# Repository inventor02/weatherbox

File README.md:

# Weatherbox

A work-in-progress hardware project to display the weather at your current location.

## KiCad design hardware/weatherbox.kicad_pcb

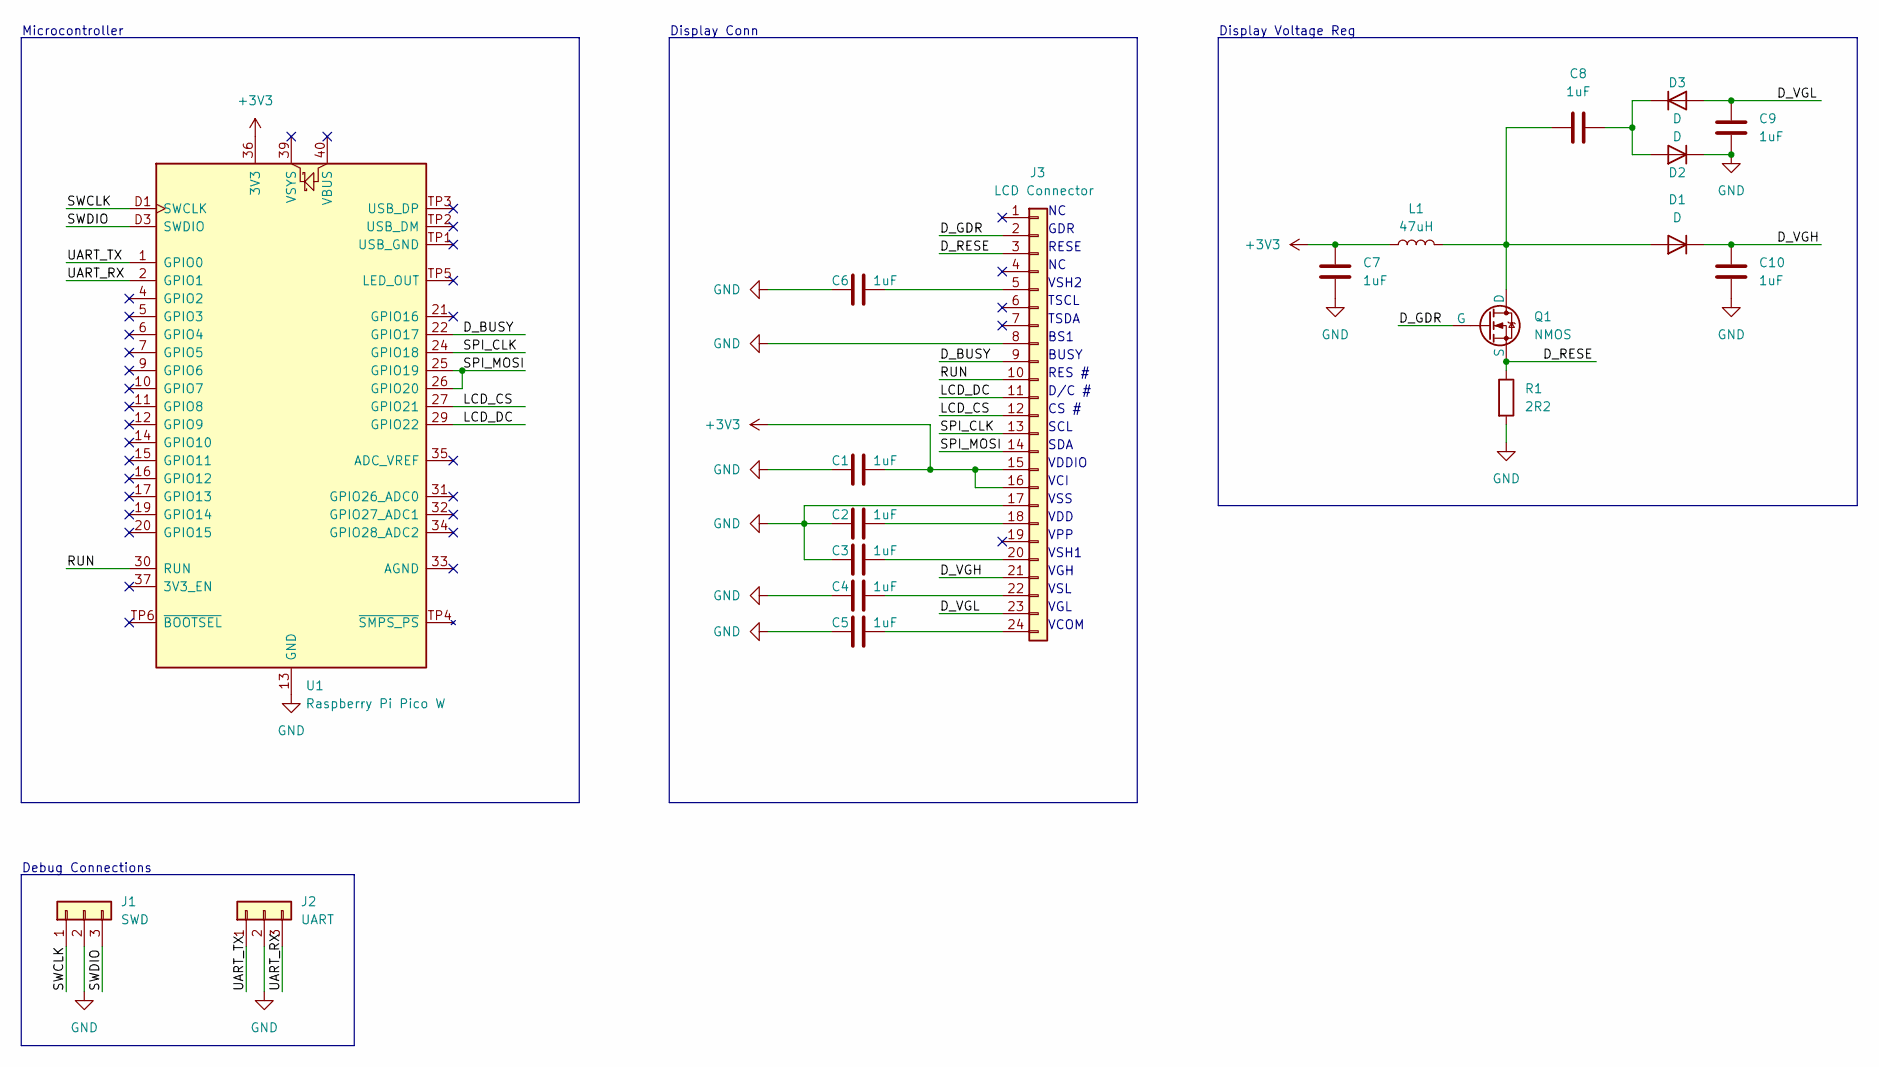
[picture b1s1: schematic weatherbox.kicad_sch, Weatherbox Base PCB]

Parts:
C1, C2, C3, C4, C5, C6, C7, C8, C9, C10: 1uF; C_0603_1608Metric_Pad1.08x0.95mm_HandSolder
D1, D2, D3: D; D_0603_1608Metric_Pad1.05x0.95mm_HandSolder
J1: SWD; JST_XH_B3B-XH-A_1x03_P2.50mm_Vertical
J2: UART; JST_XH_B3B-XH-A_1x03_P2.50mm_Vertical
J3: LCD Connector; 10051922-2410_1x24-2MP_P0.50mm_Horizontal
L1: 47uH; L_Bourns-SRN4018
Q1: NMOS; SOT-23_Handsoldering
R1: 2R2; R_0603_1608Metric_Pad0.98x0.95mm_HandSolder
U1: Raspberry Pi Pico W; RaspberryPi_Pico_W_SMD

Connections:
+3V3: C1.2, C7.1, J3.15, J3.16, L1.1, U1.36 (3V3)
/D_BUSY: J3.9, U1.22 (GPIO17)
/D_GDR: J3.2, Q1.2 (G)
/D_RESE: J3.3, Q1.3 (S), R1.1
/D_VGH: C10.1, D1.1 (K), J3.21
/D_VGL: C9.1, D3.2 (A), J3.23
/LCD_CS: J3.12, U1.27 (GPIO21)
/LCD_DC: J3.11, U1.29 (GPIO22)
/RUN: J3.10, U1.30 (RUN)
/SPI_CLK: J3.13, U1.24 (GPIO18)
/SPI_MOSI: J3.14, U1.25 (GPIO19), U1.26 (GPIO20)
/SWCLK: J1.1, U1.D1 (SWCLK)
/SWDIO: J1.3, U1.D3 (SWDIO)
/UART_RX: J2.3, U1.2 (GPIO1)
/UART_TX: J2.1, U1.1 (GPIO0)
GND: C1.1, C2.1, C3.1, C4.1, C5.1, C6.1, C7.2, C9.2, C10.2, D2.1 (K), J1.2, J2.2, J3.8, J3.17, R1.2, U1.3 (GND), U1.8 (GND), U1.13 (GND), U1.18 (GND), U1.23 (GND), U1.28 (GND), U1.38 (GND), U1.D2 (GND)
unnamed: C8.1, D1.2 (A), L1.2, Q1.1 (D)
unnamed: C8.2, D2.2 (A), D3.1 (K)
unnamed: C6.2, J3.5
unnamed: C2.2, J3.18
unnamed: C3.2, J3.20
unnamed: C4.2, J3.22
unnamed: C5.2, J3.24

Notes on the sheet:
Microcontroller
TSCL
RESE
VGH
Display Voltage Reg
VGL
BS1
TSDA
SCL
VSL
Debug Connections
VSS
VDDIO
Display Conn
GDR
VCOM
SDA
VSH1
RES #
VSH2
D/C #
VCI
VPP
VDD
CS #
BUSY

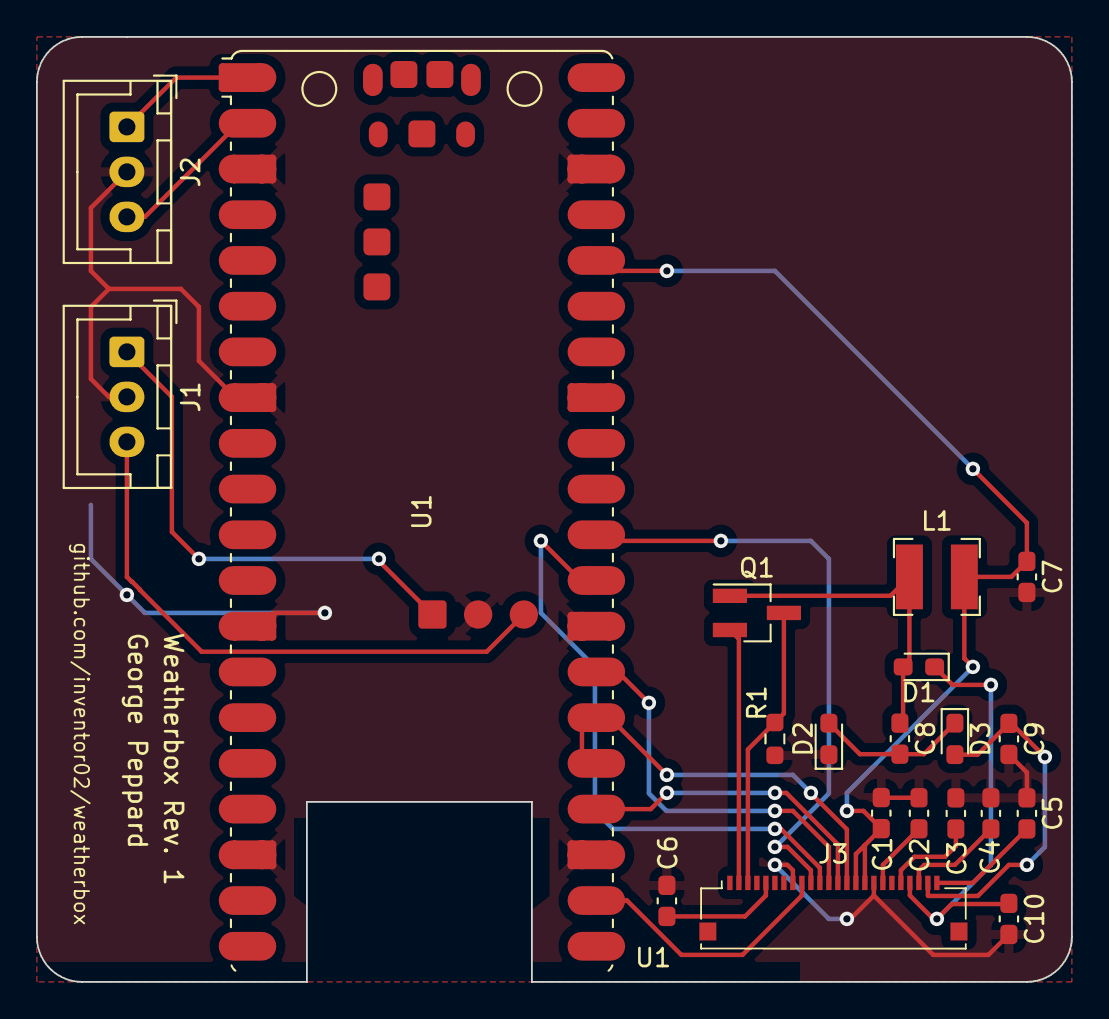
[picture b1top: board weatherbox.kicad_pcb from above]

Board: 2 copper layers, 57.5 x 52.5 mm, 20 parts (0 on the bottom side), 23 nets.

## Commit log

2023-06-17 chore: initial commit
2023-06-17 feat: update LICENSE-ing and firmware readme
2023-06-17 feat: start schematic
2023-06-18 feat: hardware rev. 1
2023-06-18 chore: out dir
2023-06-22 feat: add network connection
2023-06-22 feat:set CYW43 country

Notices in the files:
hardware/weatherbox.kicad_pcb:
Licensed under the CERN Open Hardware License Version 2 - Permissive. For details,
